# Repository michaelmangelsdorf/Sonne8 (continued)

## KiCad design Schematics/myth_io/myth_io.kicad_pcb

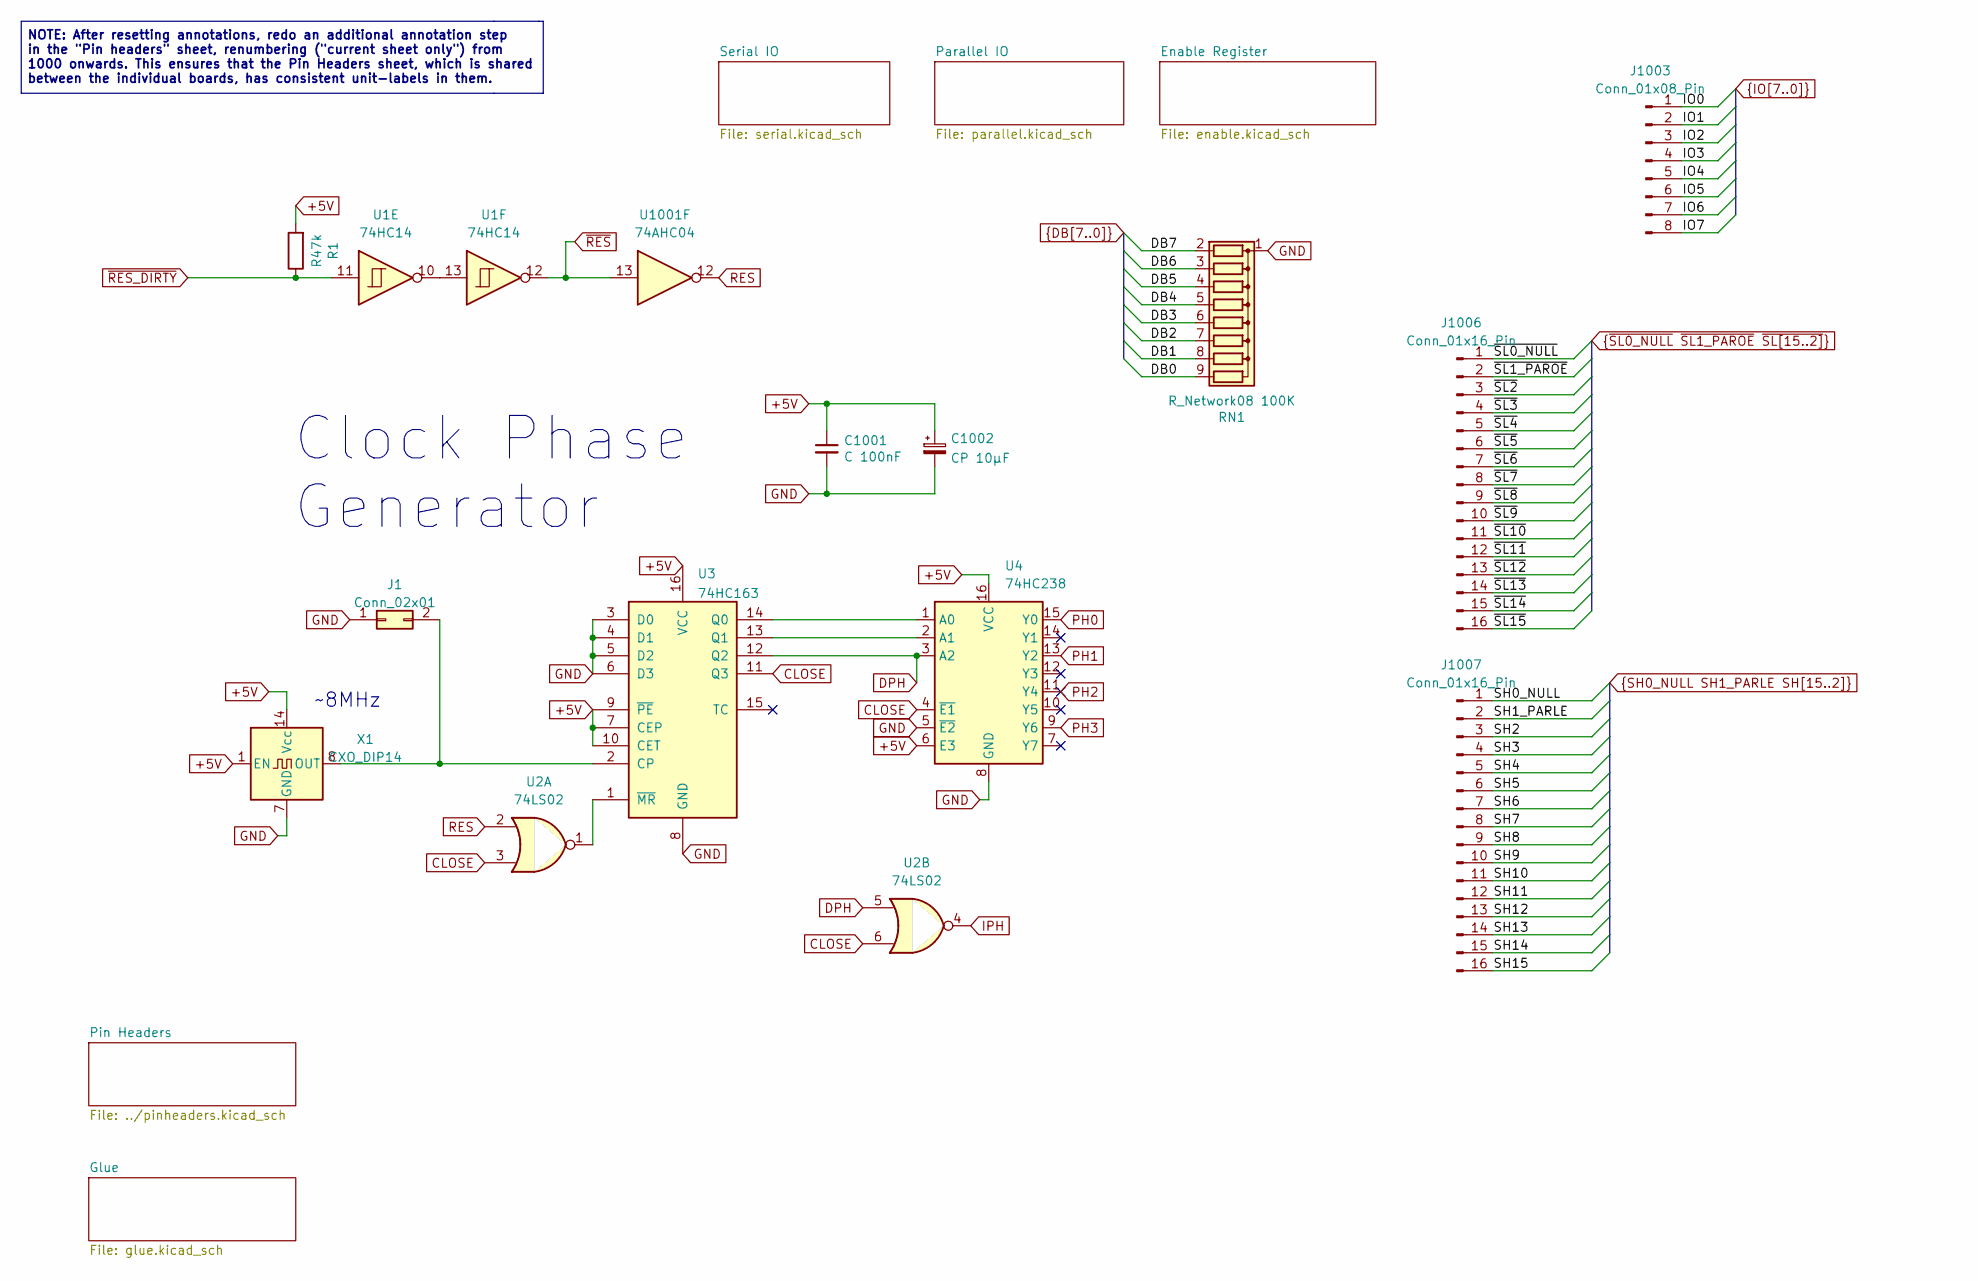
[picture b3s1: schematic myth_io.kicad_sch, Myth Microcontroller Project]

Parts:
C1001: C 100nF; C_Disc_D5.0mm_W2.5mm_P2.50mm
C1002: CP 10μF; CP_Radial_D6.3mm_P2.50mm
J1: Conn_02x01; PinHeader_2x01_P2.54mm_Vertical
J1003: Conn_01x08_Pin
J1006, J1007: Conn_01x16_Pin; PinHeader_1x16_P2.54mm_Vertical
R1: R47k; R_Axial_DIN0207_L6.3mm_D2.5mm_P10.16mm_Horizontal
RN1: R_Network08 100K; R_Array_SIP9
U1: 74HC14; DIP-14_W7.62mm_Socket_LongPads
U2: 74LS02; DIP-14_W7.62mm_Socket_LongPads
U3: 74HC163; DIP-16_W7.62mm_Socket_LongPads
U4: 74HC238; DIP-16_W7.62mm_Socket_LongPads
U1001: 74AHC04; DIP-14_W7.62mm_Socket_LongPads
X1: CXO_DIP14; Oscillator_DIP-14

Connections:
+5V: C1001.1, C1002.1, R1.2, U3.7 (CEP), U3.9 (~PE), U3.10 (CET), U3.16 (VCC), U4.6 (E3), U4.16 (VCC), X1.1 (EN), X1.14 (Vcc); also elsewhere on the board
CLOSE: U2.3, U2.6, U3.11 (Q3), U4.4 (~E1)
DB0: RN1.9 (R8); also elsewhere on the board
DB1: RN1.8 (R7); also elsewhere on the board
DB2: RN1.7 (R6); also elsewhere on the board
DB3: RN1.6 (R5); also elsewhere on the board
DB4: RN1.5 (R4); also elsewhere on the board
DB5: RN1.4 (R3); also elsewhere on the board
DB6: RN1.3 (R2); also elsewhere on the board
DB7: RN1.2 (R1); also elsewhere on the board
DPH: U2.5, U3.12 (Q2), U4.3 (A2); also elsewhere on the board
GND: C1001.2, C1002.2, J1.1, RN1.1 (common), U3.3 (D0), U3.4 (D1), U3.5 (D2), U3.6 (D3), U3.8 (GND), U4.5 (~E2), U4.8 (GND), X1.7 (GND); also elsewhere on the board
IPH: U2.4; also elsewhere on the board
unnamed: J1.2, U3.2 (CP), X1.8 (OUT)
unnamed: U1.10, U1.13
unnamed: U3.14 (Q0), U4.1 (A0)
unnamed: U3.13 (Q1), U4.2 (A1)
unnamed: U2.1, U3.1 (~MR)
PH0: U4.15 (Y0); also elsewhere on the board
PH1: U4.13 (Y2); also elsewhere on the board
PH2: U4.11 (Y4); also elsewhere on the board
PH3: U4.9 (Y6)
RES: U2.2, U1001.12; also elsewhere on the board
SH0_NULL: J1007.1; also elsewhere on the board
SH1_PARLE: J1007.2; also elsewhere on the board
SH2: J1007.3; also elsewhere on the board
SH3: J1007.4; also elsewhere on the board
SH4: J1007.5; also elsewhere on the board
SH5: J1007.6; also elsewhere on the board
SH6: J1007.7; also elsewhere on the board
SH7: J1007.8; also elsewhere on the board
SH8: J1007.9; also elsewhere on the board
SH9: J1007.10; also elsewhere on the board
SH10: J1007.11; also elsewhere on the board
SH11: J1007.12; also elsewhere on the board
SH12: J1007.13; also elsewhere on the board
SH13: J1007.14; also elsewhere on the board
SH14: J1007.15; also elsewhere on the board
SH15: J1007.16; also elsewhere on the board
~RES_DIRTY: R1.1, U1.11; also elsewhere on the board
~RES: U1.12, U1001.13; also elsewhere on the board
~SL0_NULL: J1006.1; also elsewhere on the board
~SL1_PAROE: J1006.2; also elsewhere on the board
~SL2: J1006.3; also elsewhere on the board
~SL3: J1006.4; also elsewhere on the board
~SL4: J1006.5; also elsewhere on the board
~SL5: J1006.6; also elsewhere on the board
~SL6: J1006.7; also elsewhere on the board
~SL7: J1006.8; also elsewhere on the board
~SL8: J1006.9; also elsewhere on the board
~SL9: J1006.10; also elsewhere on the board
~SL10: J1006.11; also elsewhere on the board
~SL11: J1006.12; also elsewhere on the board
~SL12: J1006.13; also elsewhere on the board
~SL13: J1006.14; also elsewhere on the board
~SL14: J1006.15; also elsewhere on the board
~SL15: J1006.16; also elsewhere on the board

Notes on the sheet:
NOTE: After resetting annotations, redo an additional annotation step in the "Pin headers" sheet, renumbering ("current sheet only") from 1000 onwards. This ensures that the Pin Headers sheet, which is shared between the individual boards, has consistent unit-labels in them.
~8MHz
Clock Phase Generator

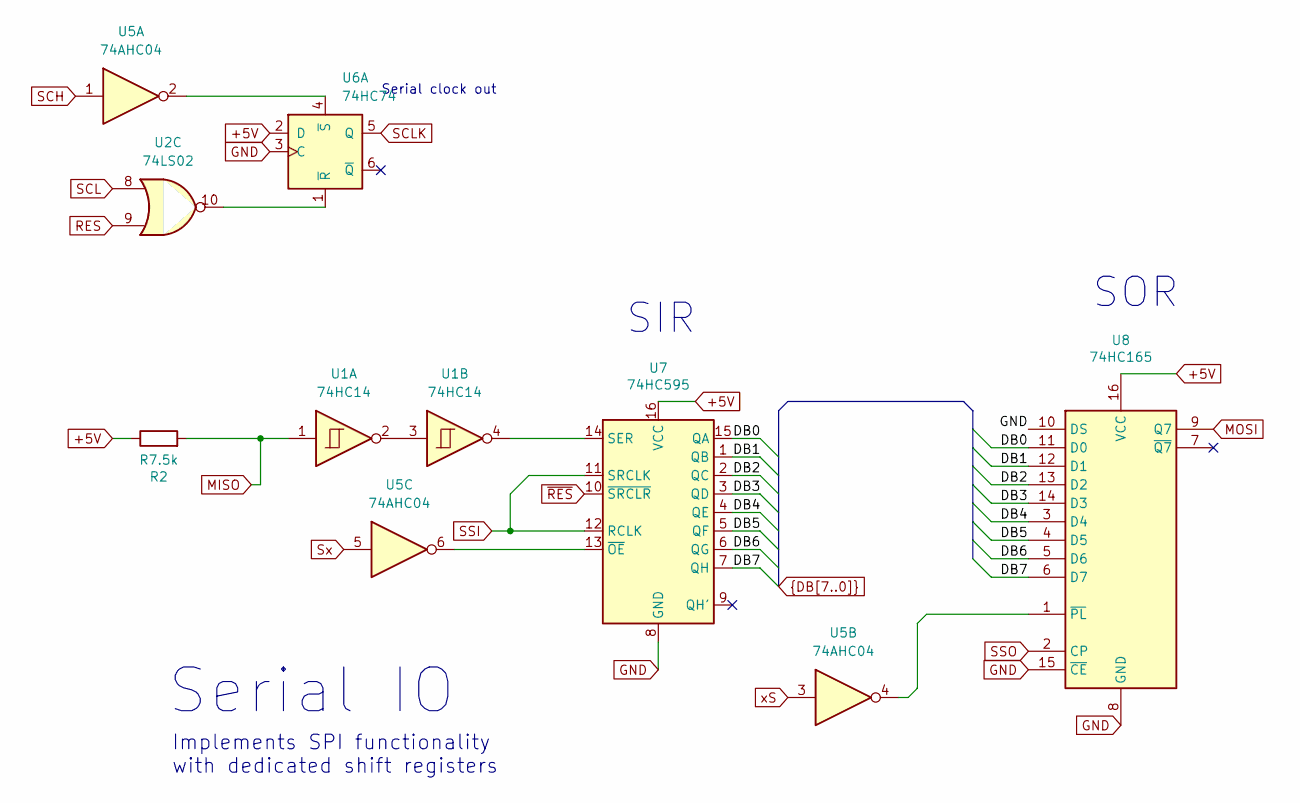
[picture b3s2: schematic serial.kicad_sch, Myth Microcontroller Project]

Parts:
R2: R7.5k; R_Axial_DIN0207_L6.3mm_D2.5mm_P10.16mm_Horizontal
U1: 74HC14; DIP-14_W7.62mm_Socket_LongPads
U2: 74LS02; DIP-14_W7.62mm_Socket_LongPads
U5: 74AHC04; DIP-14_W7.62mm_Socket_LongPads
U6: 74HC74; DIP-14_W7.62mm_Socket_LongPads
U7: 74HC595; DIP-16_W7.62mm_Socket_LongPads
U8: 74HC165; DIP-16_W7.62mm_Socket_LongPads

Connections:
+5V: R2.1, U6.2 (D), U7.16 (VCC), U8.16 (VCC); also elsewhere on the board
DB0: U7.15 (QA), U8.11 (D0); also elsewhere on the board
DB1: U7.1 (QB), U8.12 (D1); also elsewhere on the board
DB2: U7.2 (QC), U8.13 (D2); also elsewhere on the board
DB3: U7.3 (QD), U8.14 (D3); also elsewhere on the board
DB4: U7.4 (QE), U8.3 (D4); also elsewhere on the board
DB5: U7.5 (QF), U8.4 (D5); also elsewhere on the board
DB6: U7.6 (QG), U8.5 (D6); also elsewhere on the board
DB7: U7.7 (QH), U8.6 (D7); also elsewhere on the board
GND: U6.3 (C), U7.8 (GND), U8.8 (GND), U8.10 (DS), U8.15 (~CE); also elsewhere on the board
MISO: R2.2, U1.1; also elsewhere on the board
MOSI: U8.9 (Q7); also elsewhere on the board
unnamed: U1.2, U1.3
unnamed: U2.10, U6.1 (~R)
unnamed: U5.2, U6.4 (~S)
unnamed: U1.4, U7.14 (SER)
unnamed: U5.6, U7.13 (~OE)
unnamed: U5.4, U8.1 (~PL)
RES: U2.9; also elsewhere on the board
SCH: U5.1
SCL: U2.8
SCLK: U6.5 (Q); also elsewhere on the board
SSI: U7.11 (SRCLK), U7.12 (RCLK)
SSO: U8.2 (CP)
Sx: U5.5
xS: U5.3
~RES: U7.10 (~SRCLR); also elsewhere on the board

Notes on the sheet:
SOR
Serial IO
Implements SPI functionality with dedicated shift registers
SIR
Serial clock out

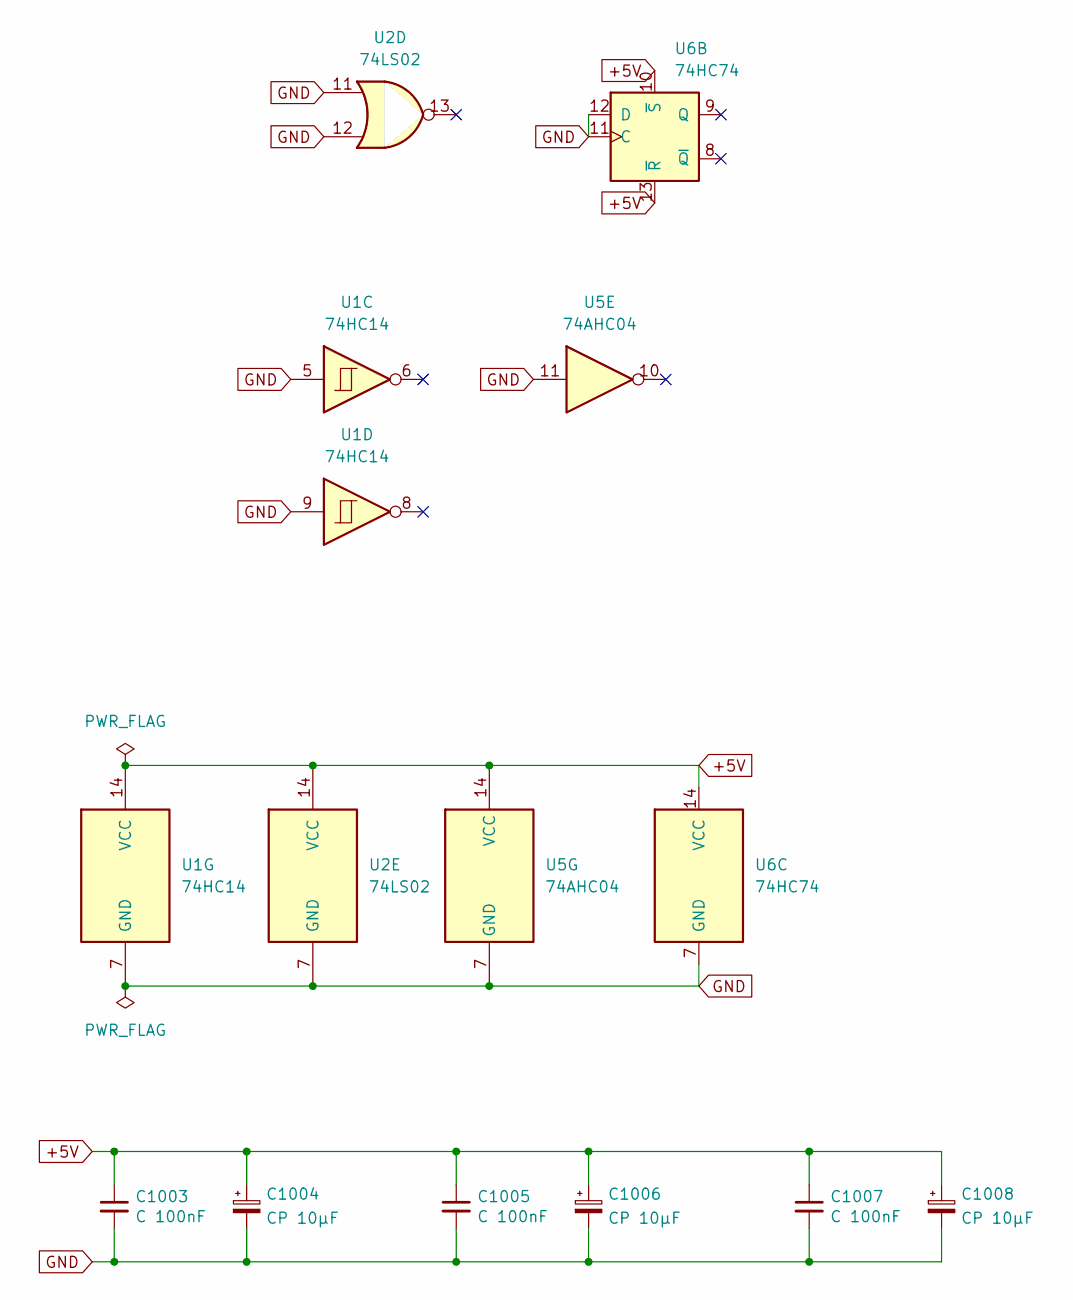
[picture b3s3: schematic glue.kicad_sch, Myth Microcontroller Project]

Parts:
C1003, C1005, C1007: C 100nF; C_Disc_D5.0mm_W2.5mm_P2.50mm
C1004, C1006, C1008: CP 10μF; CP_Radial_D6.3mm_P2.50mm
U1: 74HC14; DIP-14_W7.62mm_Socket_LongPads
U2: 74LS02; DIP-14_W7.62mm_Socket_LongPads
U5: 74AHC04; DIP-14_W7.62mm_Socket_LongPads
U6: 74HC74; DIP-14_W7.62mm_Socket_LongPads

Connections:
+5V: C1003.1, C1004.1, C1005.1, C1006.1, C1007.1, C1008.1, U1.14 (VCC), U2.14 (VCC), U5.14 (VCC), U6.10 (~S), U6.13 (~R), U6.14 (VCC); also elsewhere on the board
GND: C1003.2, C1004.2, C1005.2, C1006.2, C1007.2, C1008.2, U1.5, U1.7 (GND), U1.9, U2.7 (GND), U2.11, U2.12, U5.7 (GND), U5.11, U6.7 (GND), U6.11 (C), U6.12 (D); also elsewhere on the board

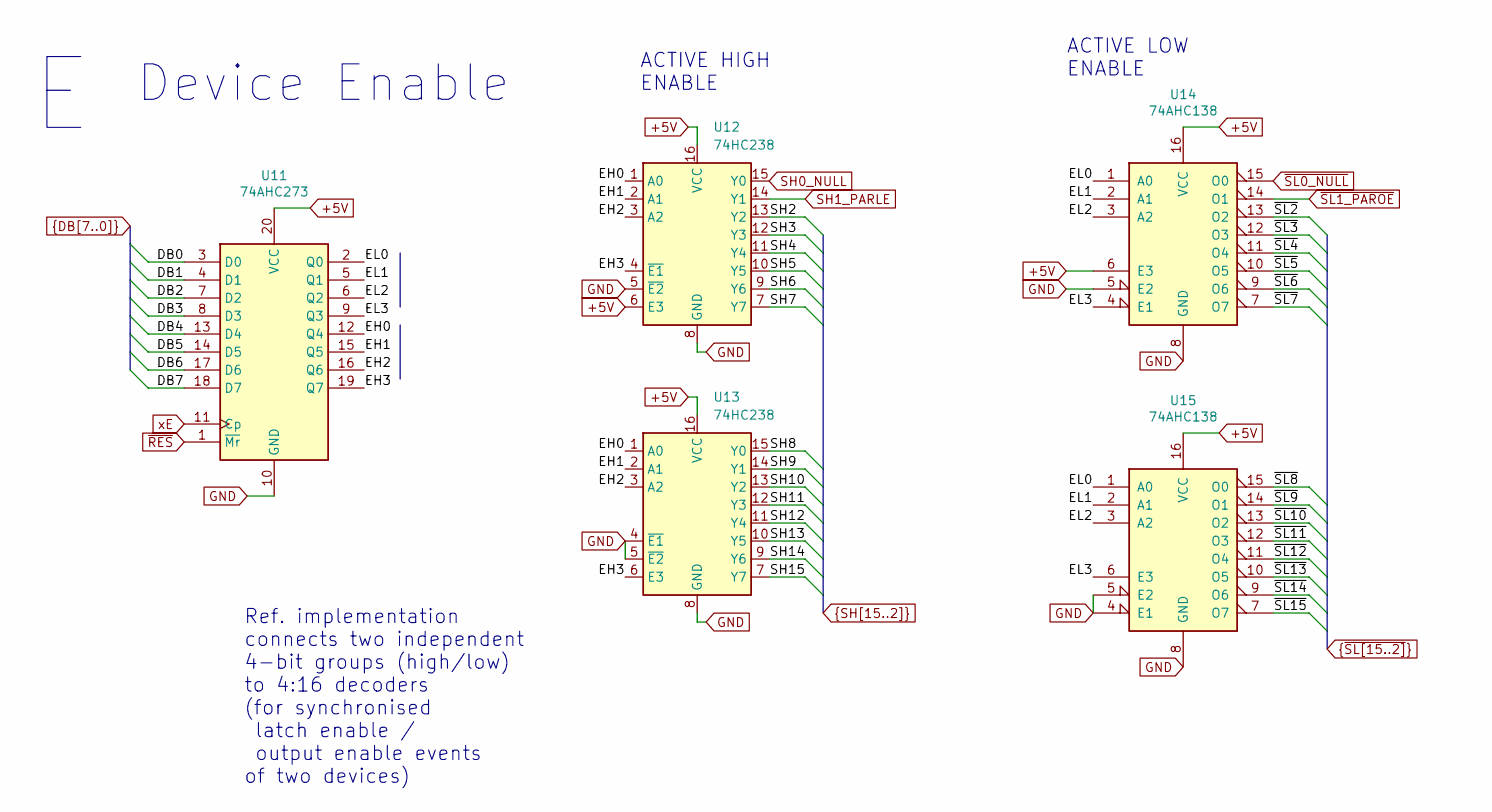
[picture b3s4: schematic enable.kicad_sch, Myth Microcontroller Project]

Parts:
U11: 74AHC273; DIP-20_W7.62mm_Socket_LongPads
U12, U13: 74HC238; DIP-16_W7.62mm_Socket_LongPads
U14, U15: 74AHC138; DIP-16_W7.62mm_Socket_LongPads

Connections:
+5V: U11.20 (VCC), U12.6 (E3), U12.16 (VCC), U13.16 (VCC), U14.6 (E3), U14.16 (VCC), U15.16 (VCC); also elsewhere on the board
/Enable Register/EH0: U11.12 (Q4), U12.1 (A0), U13.1 (A0)
/Enable Register/EH1: U11.15 (Q5), U12.2 (A1), U13.2 (A1)
/Enable Register/EH2: U11.16 (Q6), U12.3 (A2), U13.3 (A2)
/Enable Register/EH3: U11.19 (Q7), U12.4 (~E1), U13.6 (E3)
/Enable Register/EL0: U11.2 (Q0), U14.1 (A0), U15.1 (A0)
/Enable Register/EL1: U11.5 (Q1), U14.2 (A1), U15.2 (A1)
/Enable Register/EL2: U11.6 (Q2), U14.3 (A2), U15.3 (A2)
/Enable Register/EL3: U11.9 (Q3), U14.4 (E1), U15.6 (E3)
DB0: U11.3 (D0); also elsewhere on the board
DB1: U11.4 (D1); also elsewhere on the board
DB2: U11.7 (D2); also elsewhere on the board
DB3: U11.8 (D3); also elsewhere on the board
DB4: U11.13 (D4); also elsewhere on the board
DB5: U11.14 (D5); also elsewhere on the board
DB6: U11.17 (D6); also elsewhere on the board
DB7: U11.18 (D7); also elsewhere on the board
GND: U11.10 (GND), U12.5 (~E2), U12.8 (GND), U13.4 (~E1), U13.5 (~E2), U13.8 (GND), U14.5 (E2), U14.8 (GND), U15.4 (E1), U15.5 (E2), U15.8 (GND); also elsewhere on the board
SH0_NULL: U12.15 (Y0); also elsewhere on the board
SH1_PARLE: U12.14 (Y1); also elsewhere on the board
SH2: U12.13 (Y2); also elsewhere on the board
SH3: U12.12 (Y3); also elsewhere on the board
SH4: U12.11 (Y4); also elsewhere on the board
SH5: U12.10 (Y5); also elsewhere on the board
SH6: U12.9 (Y6); also elsewhere on the board
SH7: U12.7 (Y7); also elsewhere on the board
SH8: U13.15 (Y0); also elsewhere on the board
SH9: U13.14 (Y1); also elsewhere on the board
SH10: U13.13 (Y2); also elsewhere on the board
SH11: U13.12 (Y3); also elsewhere on the board
SH12: U13.11 (Y4); also elsewhere on the board
SH13: U13.10 (Y5); also elsewhere on the board
SH14: U13.9 (Y6); also elsewhere on the board
SH15: U13.7 (Y7); also elsewhere on the board
xE: U11.11 (Cp); also elsewhere on the board
~RES: U11.1 (~Mr); also elsewhere on the board
~SL0_NULL: U14.15 (O0); also elsewhere on the board
~SL1_PAROE: U14.14 (O1); also elsewhere on the board
~SL2: U14.13 (O2); also elsewhere on the board
~SL3: U14.12 (O3); also elsewhere on the board
~SL4: U14.11 (O4); also elsewhere on the board
~SL5: U14.10 (O5); also elsewhere on the board
~SL6: U14.9 (O6); also elsewhere on the board
~SL7: U14.7 (O7); also elsewhere on the board
~SL8: U15.15 (O0); also elsewhere on the board
~SL9: U15.14 (O1); also elsewhere on the board
~SL10: U15.13 (O2); also elsewhere on the board
~SL11: U15.12 (O3); also elsewhere on the board
~SL12: U15.11 (O4); also elsewhere on the board
~SL13: U15.10 (O5); also elsewhere on the board
~SL14: U15.9 (O6); also elsewhere on the board
~SL15: U15.7 (O7); also elsewhere on the board

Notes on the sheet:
ACTIVE LOW ENABLE
Ref. implementation connects two independent 4-bit groups (high/low) to 4:16 decoders (for synchronised latch enable / output enable events of two devices)
Device Enable
ACTIVE HIGH ENABLE

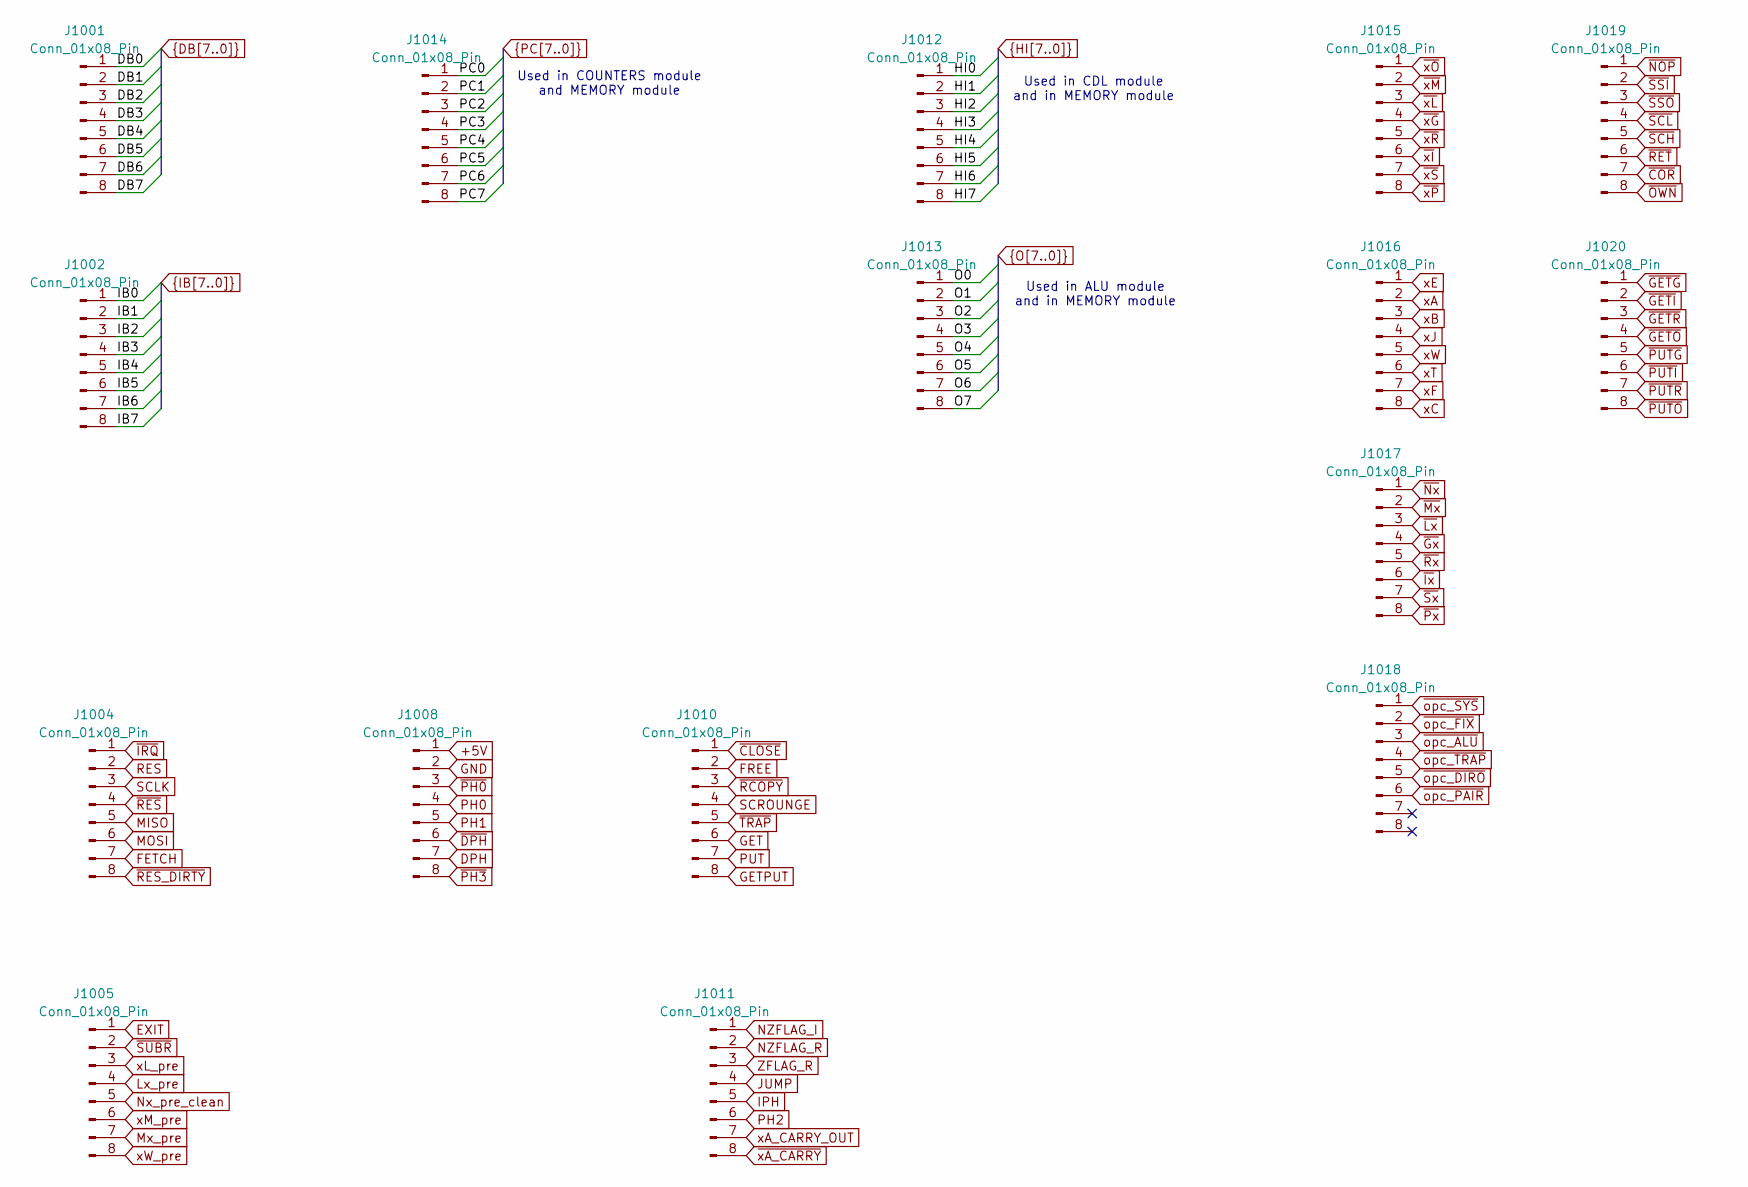
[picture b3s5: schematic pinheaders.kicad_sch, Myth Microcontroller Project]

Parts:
J1001, J1002, J1004, J1005, J1008, J1010, J1011, J1012, J1013, J1014, J1015, J1016, J1017, J1018, J1019, J1020: Conn_01x08_Pin; PinHeader_1x08_P2.54mm_Vertical

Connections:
+5V: J1008.1; also elsewhere on the board
DB0: J1001.1; also elsewhere on the board
DB1: J1001.2; also elsewhere on the board
DB2: J1001.3; also elsewhere on the board
DB3: J1001.4; also elsewhere on the board
DB4: J1001.5; also elsewhere on the board
DB5: J1001.6; also elsewhere on the board
DB6: J1001.7; also elsewhere on the board
DB7: J1001.8; also elsewhere on the board
DPH: J1008.7; also elsewhere on the board
EXIT: J1005.1
FETCH: J1004.7
FREE: J1010.2
GET: J1010.6
GETPUT: J1010.8
GND: J1008.2; also elsewhere on the board
HI0: J1012.1
HI1: J1012.2
HI2: J1012.3
HI3: J1012.4
HI4: J1012.5
HI5: J1012.6
HI6: J1012.7
HI7: J1012.8
IB0: J1002.1
IB1: J1002.2
IB2: J1002.3
IB3: J1002.4
IB4: J1002.5
IB5: J1002.6
IB6: J1002.7
IB7: J1002.8
IPH: J1011.5; also elsewhere on the board
JUMP: J1011.4
Lx_pre: J1005.4
MISO: J1004.5; also elsewhere on the board
MOSI: J1004.6; also elsewhere on the board
Mx_pre: J1005.7
NZFLAG_I: J1011.1
NZFLAG_R: J1011.2
Nx_pre_clean: J1005.5
O0: J1013.1
O1: J1013.2
O2: J1013.3
O3: J1013.4
O4: J1013.5
O5: J1013.6
O6: J1013.7
O7: J1013.8
PC0: J1014.1
PC1: J1014.2
PC2: J1014.3
PC3: J1014.4
PC4: J1014.5
PC5: J1014.6
PC6: J1014.7
PC7: J1014.8
PH0: J1008.4; also elsewhere on the board
PH1: J1008.5; also elsewhere on the board
PH2: J1011.6; also elsewhere on the board
PUT: J1010.7
RES: J1004.2; also elsewhere on the board
SCLK: J1004.3; also elsewhere on the board
SCROUNGE: J1010.4
ZFLAG_R: J1011.3
xA: J1016.2
xA_CARRY_OUT: J1011.7
xB: J1016.3
xC: J1016.8
xE: J1016.1; also elsewhere on the board
xF: J1016.7
xJ: J1016.4
xL_pre: J1005.3
xM_pre: J1005.6
xT: J1016.6
xW: J1016.5
xW_pre: J1005.8
~CLOSE: J1010.1
~COR: J1019.7
~DPH: J1008.6
~Dx: J1017.4
~GETD: J1020.1
~GETI: J1020.2
~GETO: J1020.4
~GETR: J1020.3
~IRQ: J1004.1
~Ix: J1017.6
~Lx: J1017.3
~Mx: J1017.2
~NOP: J1019.1
~Nx: J1017.1
~OWN: J1019.8
~PH0: J1008.3
~PH3: J1008.8
~PUTD: J1020.5
~PUTI: J1020.6
~PUTO: J1020.8
~PUTR: J1020.7
~Px: J1017.8
~RCOPY: J1010.3
~RES_DIRTY: J1004.8; also elsewhere on the board
~RES: J1004.4; also elsewhere on the board
~RET: J1019.6
~Rx: J1017.5
~SCH: J1019.5
~SCL: J1019.4
~SSI: J1019.2
~SSO: J1019.3
~SUBR: J1005.2
~Sx: J1017.7
~TRAP: J1010.5
~opc_ALU: J1018.3
~opc_DIRO: J1018.5
~opc_FIX: J1018.2
~opc_PAIR: J1018.6
~opc_SYS: J1018.1
~opc_TRAP: J1018.4
~xA_CARRY: J1011.8
~xD: J1015.4
~xI: J1015.6
~xL: J1015.3
~xM: J1015.2
~xO: J1015.1
~xP: J1015.8
~xR: J1015.5
~xS: J1015.7

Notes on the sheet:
Used in COUNTERS module and MEMORY module
Used in CDL module and in MEMORY module
Used in ALU module and in MEMORY module

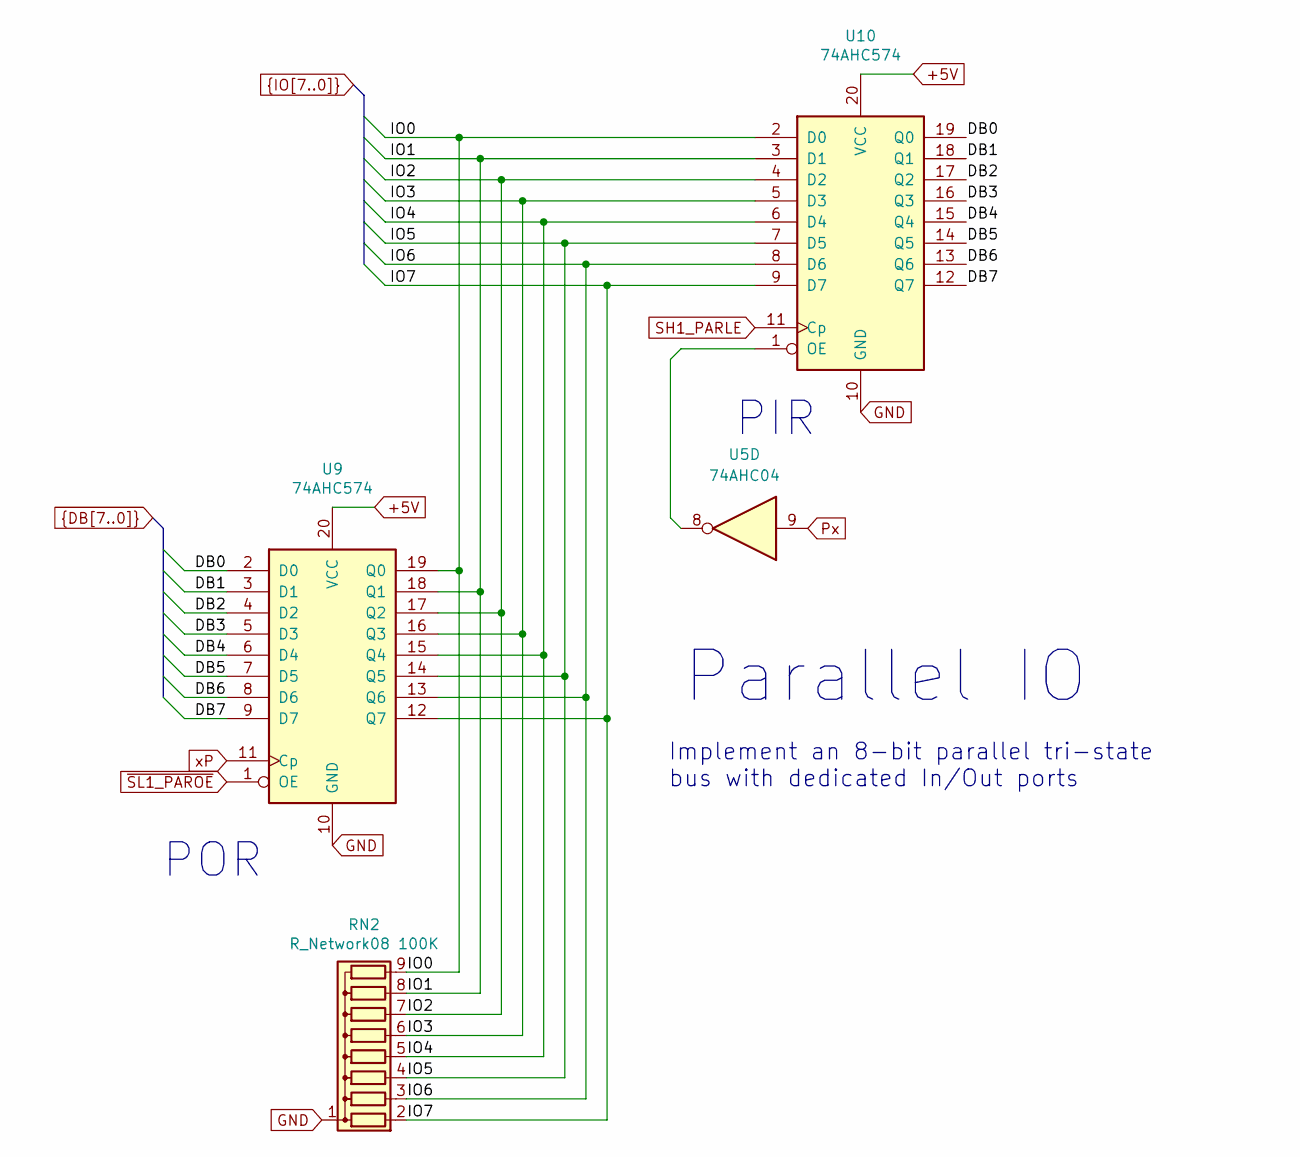
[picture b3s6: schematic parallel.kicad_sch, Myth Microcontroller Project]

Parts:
RN2: R_Network08 100K; R_Array_SIP9
U5: 74AHC04; DIP-14_W7.62mm_Socket_LongPads
U9, U10: 74AHC574; DIP-20_W7.62mm_Socket_LongPads

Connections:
+5V: U9.20 (VCC), U10.20 (VCC); also elsewhere on the board
DB0: U9.2 (D0), U10.19 (Q0); also elsewhere on the board
DB1: U9.3 (D1), U10.18 (Q1); also elsewhere on the board
DB2: U9.4 (D2), U10.17 (Q2); also elsewhere on the board
DB3: U9.5 (D3), U10.16 (Q3); also elsewhere on the board
DB4: U9.6 (D4), U10.15 (Q4); also elsewhere on the board
DB5: U9.7 (D5), U10.14 (Q5); also elsewhere on the board
DB6: U9.8 (D6), U10.13 (Q6); also elsewhere on the board
DB7: U9.9 (D7), U10.12 (Q7); also elsewhere on the board
GND: RN2.1 (common), U9.10 (GND), U10.10 (GND); also elsewhere on the board
IO0: RN2.9 (R8), U9.19 (Q0), U10.2 (D0)
IO1: RN2.8 (R7), U9.18 (Q1), U10.3 (D1)
IO2: RN2.7 (R6), U9.17 (Q2), U10.4 (D2)
IO3: RN2.6 (R5), U9.16 (Q3), U10.5 (D3)
IO4: RN2.5 (R4), U9.15 (Q4), U10.6 (D4)
IO5: RN2.4 (R3), U9.14 (Q5), U10.7 (D5)
IO6: RN2.3 (R2), U9.13 (Q6), U10.8 (D6)
IO7: RN2.2 (R1), U9.12 (Q7), U10.9 (D7)
unnamed: U5.8, U10.1 (OE)
Px: U5.9
SH1_PARLE: U10.11 (Cp); also elsewhere on the board
xP: U9.11 (Cp)
~SL1_PAROE: U9.1 (OE); also elsewhere on the board

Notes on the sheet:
Implement an 8-bit parallel tri-state bus with dedicated In/Out ports
PIR
POR
Parallel IO

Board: 2 copper layers, 46 parts (0 on the bottom side), 84 nets, no tracks yet.

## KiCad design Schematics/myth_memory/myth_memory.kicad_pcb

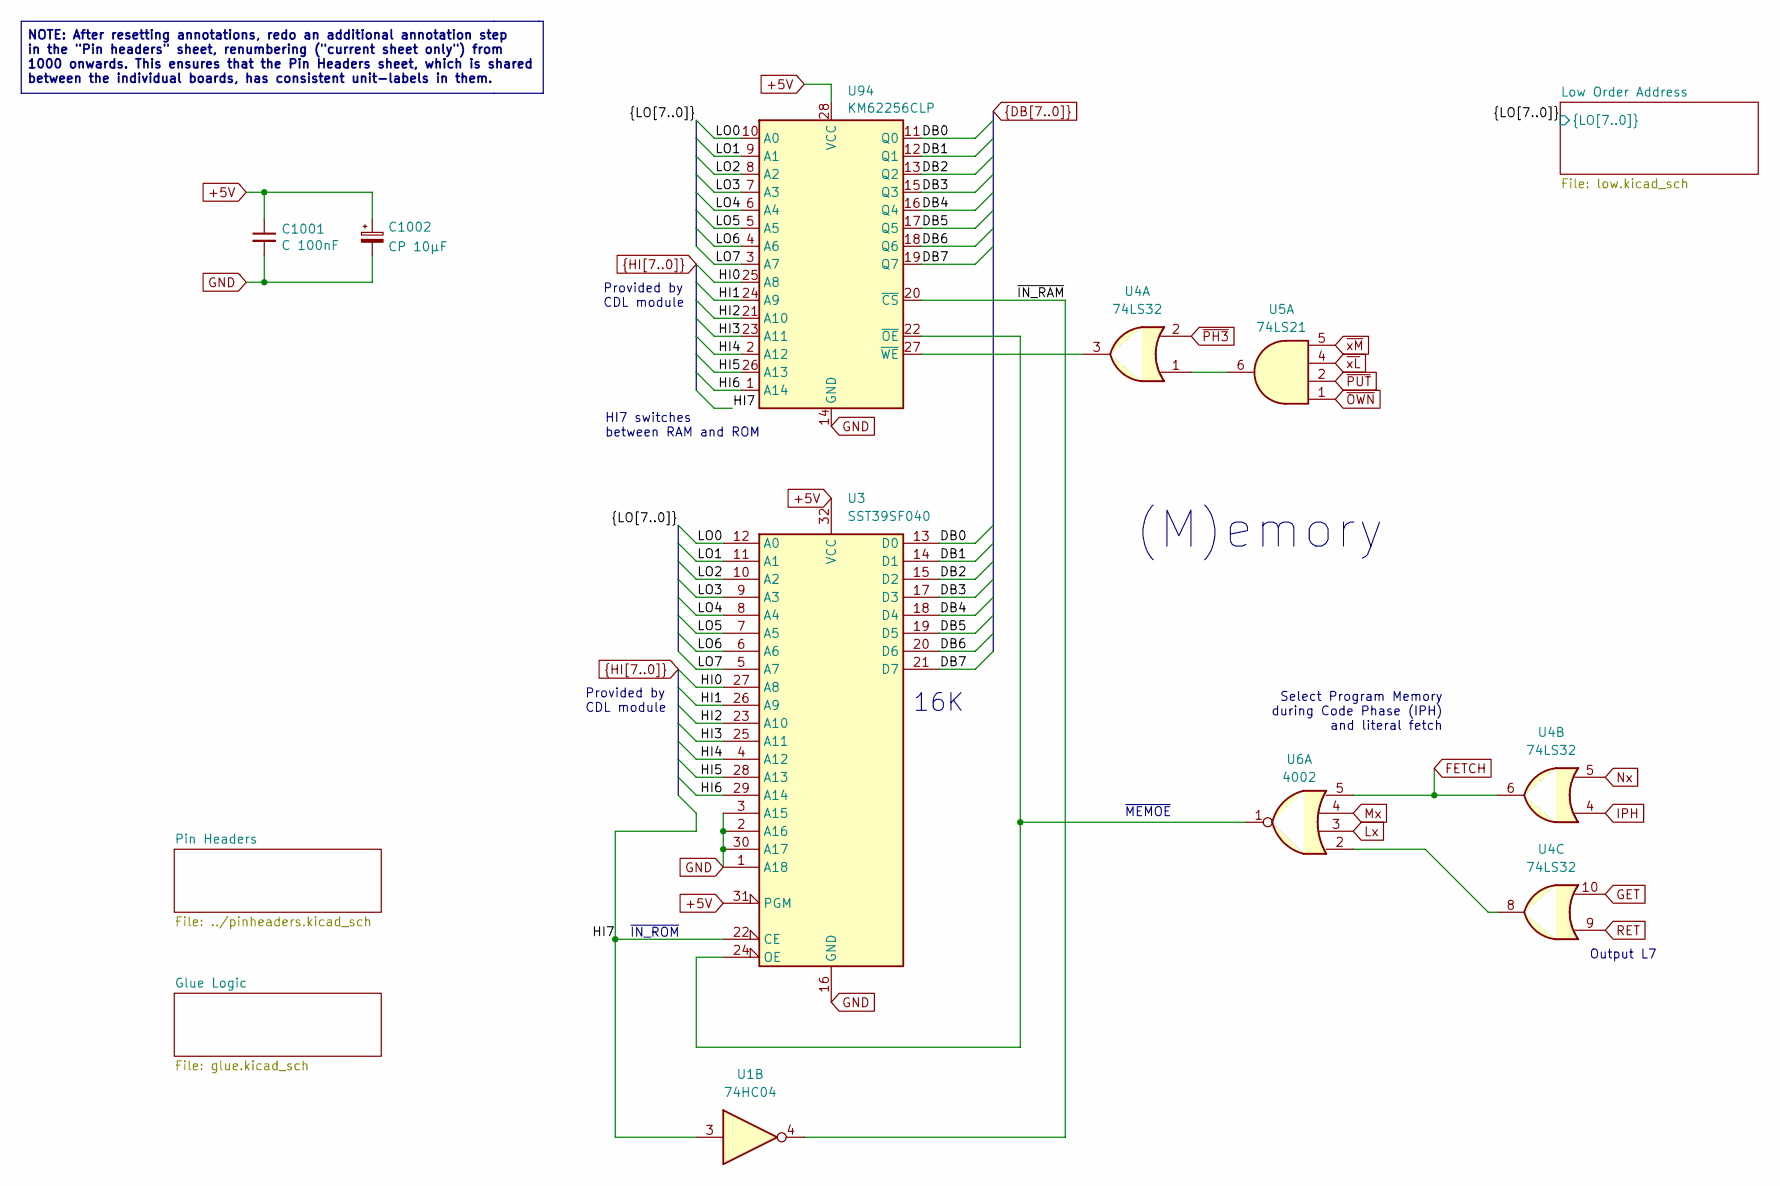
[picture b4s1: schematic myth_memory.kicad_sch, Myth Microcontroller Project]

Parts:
C1001: C 100nF; C_Disc_D5.0mm_W2.5mm_P2.50mm
C1002: CP 10μF; CP_Radial_D6.3mm_P2.50mm
U1: 74HC04; DIP-14_W7.62mm_LongPads
U3: SST39SF040; DIP-32_W15.24mm_LongPads
U4: 74LS32; DIP-14_W7.62mm_LongPads
U5: 74LS21; DIP-14_W7.62mm_LongPads
U6: 4002; DIP-14_W7.62mm_LongPads
U94: KM62256CLP; DIP-28_W15.24mm_LongPads

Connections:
+5V: C1001.1, C1002.1, U3.31 (PGM), U3.32 (VCC); also elsewhere on the board
/LO0: U3.12 (A0); also elsewhere on the board
/LO1: U3.11 (A1); also elsewhere on the board
/LO2: U3.10 (A2); also elsewhere on the board
/LO3: U3.9 (A3); also elsewhere on the board
/LO4: U3.8 (A4); also elsewhere on the board
/LO5: U3.7 (A5); also elsewhere on the board
/LO6: U3.6 (A6); also elsewhere on the board
/LO7: U3.5 (A7); also elsewhere on the board
/~IN_RAM: U1.4; also elsewhere on the board
DB0: U3.13 (D0); also elsewhere on the board
DB1: U3.14 (D1); also elsewhere on the board
DB2: U3.15 (D2); also elsewhere on the board
DB3: U3.17 (D3); also elsewhere on the board
DB4: U3.18 (D4); also elsewhere on the board
DB5: U3.19 (D5); also elsewhere on the board
DB6: U3.20 (D6); also elsewhere on the board
DB7: U3.21 (D7); also elsewhere on the board
FETCH: U4.6, U6.5; also elsewhere on the board
GET: U4.10; also elsewhere on the board
GND: C1001.2, C1002.2, U3.1 (A18), U3.2 (A16), U3.3 (A15), U3.16 (GND), U3.30 (A17); also elsewhere on the board
HI0: U3.27 (A8); also elsewhere on the board
HI1: U3.26 (A9); also elsewhere on the board
HI2: U3.23 (A10); also elsewhere on the board
HI3: U3.25 (A11); also elsewhere on the board
HI4: U3.4 (A12); also elsewhere on the board
HI5: U3.28 (A13); also elsewhere on the board
HI6: U3.29 (A14); also elsewhere on the board
HI7: U1.3, U3.22 (CE); also elsewhere on the board
IPH: U4.4; also elsewhere on the board
Lx: U6.3
Mx: U6.4
unnamed 55: U3.24 (OE), U6.1; also elsewhere on the board
unnamed 56: U4.3; also elsewhere on the board
unnamed: U4.1, U5.6
unnamed: U4.8, U6.2
Nx: U4.5
RET: U4.9; also elsewhere on the board
~OWN: U5.1; also elsewhere on the board
~PH3: U4.2; also elsewhere on the board
~PUT: U5.2
~xL: U5.4; also elsewhere on the board
~xM: U5.5; also elsewhere on the board

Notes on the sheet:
Output L7
~{MEMOE}
Provided by CDL module
16K
HI7 switches between RAM and ROM
Select Program Memory during Code Phase (IPH) and literal fetch
NOTE: After resetting annotations, redo an additional annotation step in the "Pin headers" sheet, renumbering ("current sheet only") from 1000 onwards. This ensures that the Pin Headers sheet, which is shared between the individual boards, has consistent unit-labels in them.
(M)emory
~{IN_ROM}
